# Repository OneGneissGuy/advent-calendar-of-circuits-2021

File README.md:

# advent-calendar-of-circuits-2021
Challenge to build a circuit board design and layout each day (on average) for 31 days in December. most of these circuits are based around operational and instrumentation amplifiers, but there are a few others that are more complex.

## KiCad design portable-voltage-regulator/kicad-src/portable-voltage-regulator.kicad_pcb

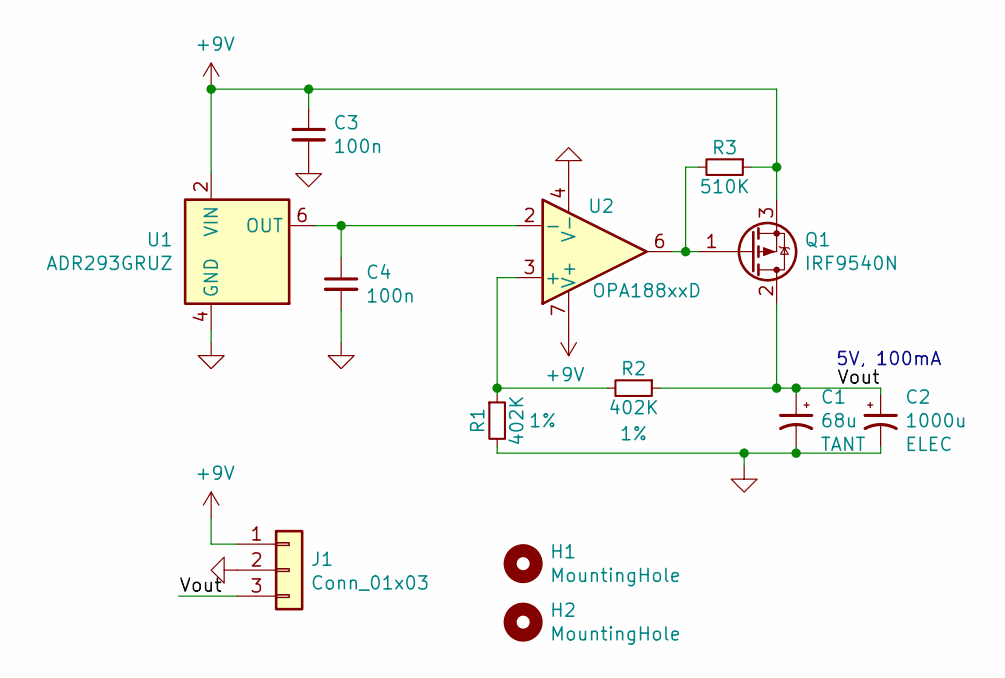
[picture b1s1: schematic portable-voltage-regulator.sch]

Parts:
C1: 68u; CP_EIA-3528-12_Kemet-T_Pad1.50x2.35mm_HandSolder
C2: 1000u; CP_Elec_6.3x5.4_Nichicon
C3, C4: 100n; C_0603_1608Metric
H1, H2: MountingHole; MountingHole_2.7mm_M2.5
J1: Conn_01x03; PinSocket_1x03_P2.54mm_Vertical
Q1: IRF9540N; TO-220-3_Vertical
R1, R2: 402K; R_0603_1608Metric
R3: 510K; R_0603_1608Metric
U1: ADR293GRUZ; TSSOP-8_4.4x3mm_P0.65mm
U2: OPA188xxD; SOIC-8_3.9x4.9mm_P1.27mm

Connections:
+9V: C3.1, J1.1, Q1.3 (S), R3.1, U1.2 (VIN), U2.7 (V+)
/Vout: C1.1, C2.1, J1.3, Q1.2 (D), R2.1
GND: C1.2, C2.2, C3.2, C4.2, J1.2, R1.2, U1.4 (GND), U2.4 (V-)
unnamed: C4.1, U1.6 (OUT), U2.2 (-)
unnamed: Q1.1 (G), R3.2, U2.6
unnamed: R1.1, R2.2, U2.3 (+)

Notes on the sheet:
5V, 100mA

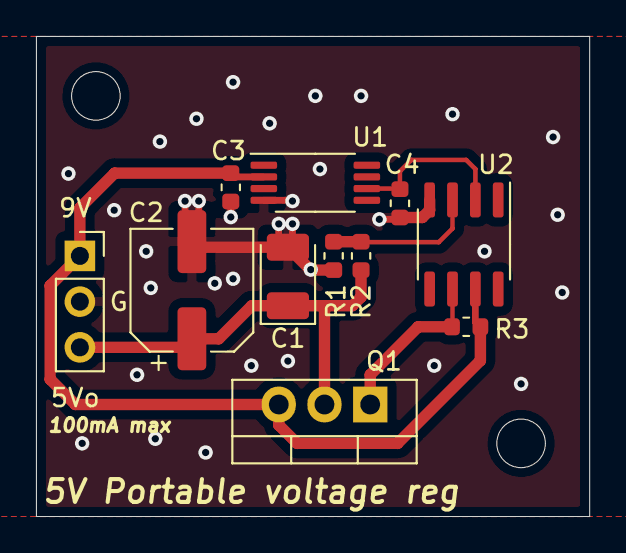
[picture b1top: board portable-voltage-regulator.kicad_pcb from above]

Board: 2 copper layers, 30.7 x 26.7 mm, 13 parts (0 on the bottom side), 6 nets.

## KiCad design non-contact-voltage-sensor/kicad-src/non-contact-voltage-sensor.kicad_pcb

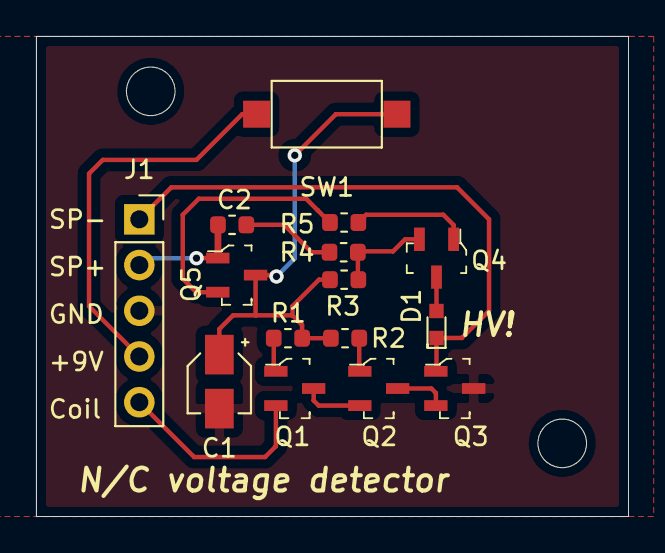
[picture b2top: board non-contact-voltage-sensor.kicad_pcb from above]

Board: 2 copper layers, 32.9 x 26.7 mm, 17 parts (0 on the bottom side), 15 nets.

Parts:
C1: 10uF; CP_Elec_3x5.3
C2: 47nF; C_0603_1608Metric
D1: LED_ALT; LED_0603
H1, H2: MountingHole; MountingHole_2.7mm_M2.5
J1: Conn_01x05; PinSocket_1x05_P2.54mm_Vertical
Q1, Q2, Q3, Q4: BC547BTA; SOT-23-3
Q5: BC557BTA; SOT-23-3
R1: 1M; R_0603_1608Metric
R2: 100K; R_0603_1608Metric
R3: 56K; R_0603_1608Metric
R4: 1K; R_0603_1608Metric
R5: 100R; R_0603_1608Metric
SW1: SW_SPST; SW_SPST_CK_RS282G05A3

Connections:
+9V: J1.4, SW1.2
/Coil: J1.5, Q1.2
/SP+: C2.2, J1.2, Q5.1
/SP-: D1.1, J1.1, Q3.1
GND: C1.2, J1.3, Q3.3
unnamed: C1.1, Q5.3, R1.1, R2.1, R3.1, SW1.1
unnamed: C2.1, R4.1
unnamed: D1.2, Q4.3
unnamed: Q1.1, R1.2
unnamed: Q1.3, Q2.2
unnamed: Q2.1, R2.2
unnamed: Q2.3, Q3.2
unnamed: Q4.1, R5.2
unnamed: Q4.2, R3.2, R4.2
unnamed: Q5.2, R5.1

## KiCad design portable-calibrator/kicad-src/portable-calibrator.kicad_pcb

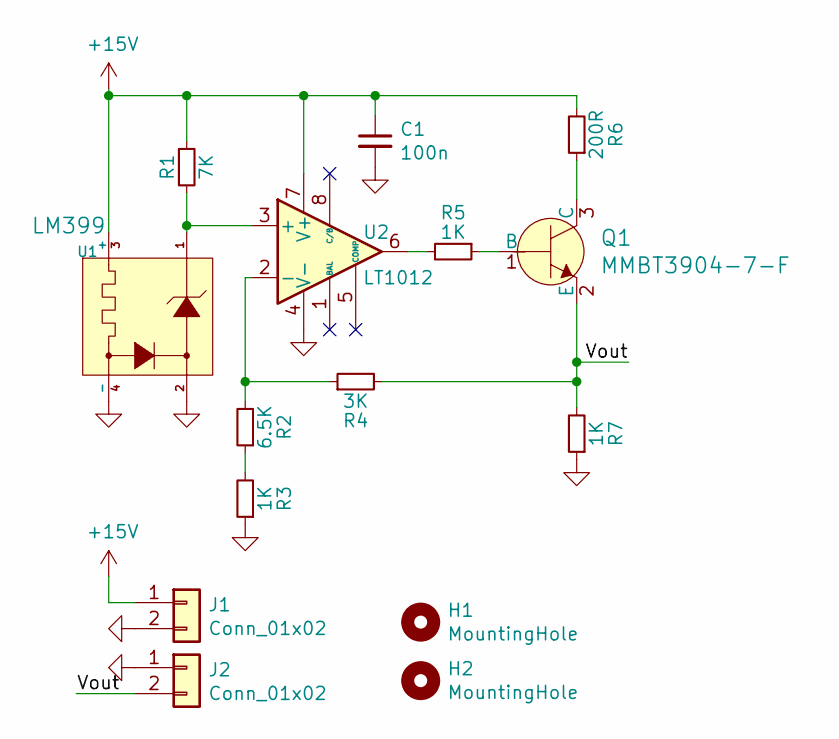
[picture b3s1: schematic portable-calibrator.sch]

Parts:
C1: 100n; C_0603_1608Metric
H1, H2: MountingHole; MountingHole_2.7mm_M2.5
J1, J2: Conn_01x02; PinSocket_1x02_P2.54mm_Vertical
Q1: MMBT3904-7-F; SOT-23-3; MPN MMBT3904-7-F; Digi-Key_PN MMBT3904-FDICT-ND
R1: 7K; R_0603_1608Metric
R2: 6.5K; R_0603_1608Metric
R3, R5, R7: 1K; R_0603_1608Metric
R4: 3K; R_0603_1608Metric
R6: 200R; R_0603_1608Metric
U1: LM399; TO-46-4
U2: LT1012; SOIC-8_3.9x4.9mm_P1.27mm

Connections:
+15V: C1.1, J1.1, R1.1, R6.2, U1.3 (+), U2.7 (V+)
/Vout: J2.2, Q1.2 (E), R4.2, R7.2
GND: C1.2, J1.2, J2.1, R3.1, R7.1, U1.2, U1.4 (-), U2.4 (V-)
unnamed: Q1.1 (B), R5.1
unnamed: Q1.3 (C), R6.1
unnamed: R1.2, U1.1, U2.3 (+)
unnamed: R2.1, R3.2
unnamed: R2.2, R4.1, U2.2 (-)
unnamed: R5.2, U2.6

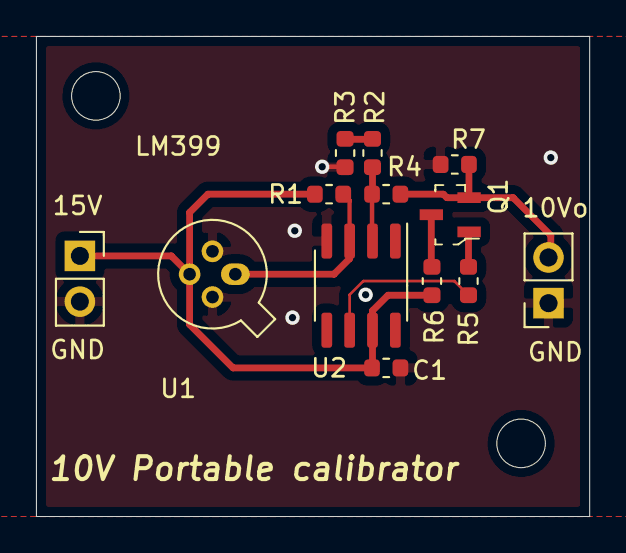
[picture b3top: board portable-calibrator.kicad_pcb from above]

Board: 2 copper layers, 30.7 x 26.7 mm, 15 parts (0 on the bottom side), 9 nets.

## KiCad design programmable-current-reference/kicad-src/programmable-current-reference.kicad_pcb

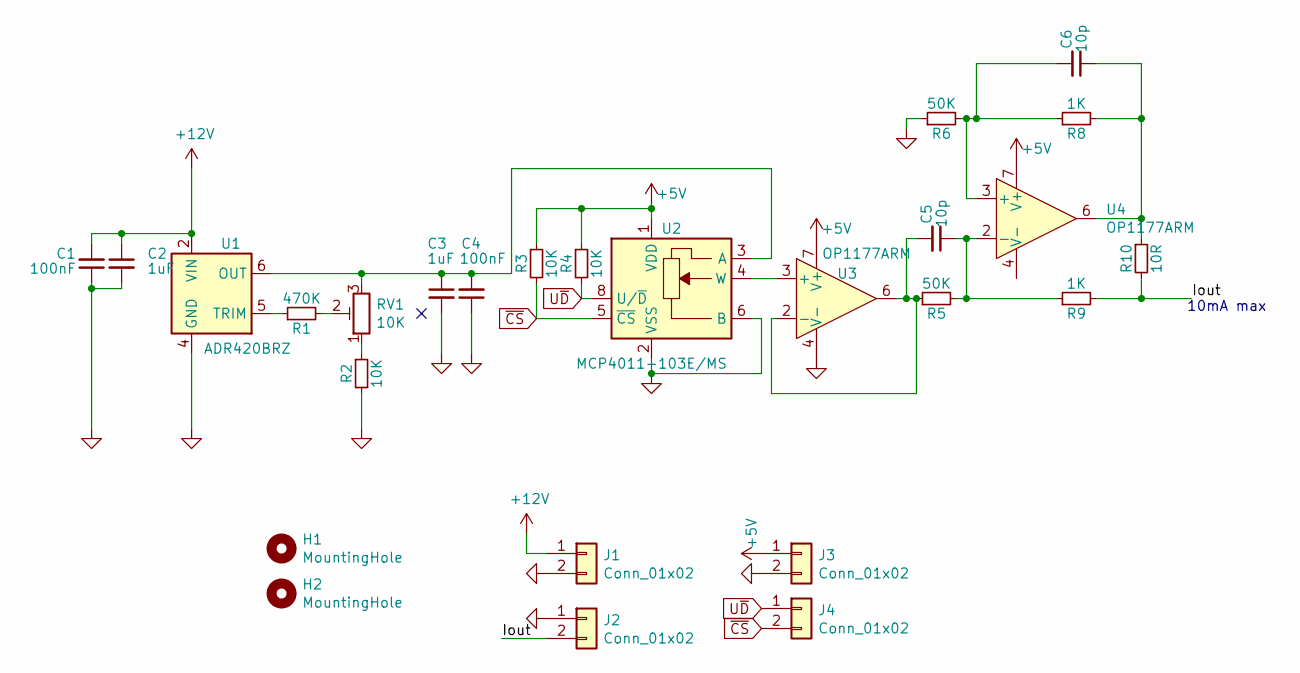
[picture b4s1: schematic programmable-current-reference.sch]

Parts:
C1, C4: 100nF; C_0603_1608Metric
C2, C3: 1uF; C_0603_1608Metric
C5, C6: 10p; C_0603_1608Metric
H1, H2: MountingHole; MountingHole_2.7mm_M2.5
J1, J2, J3, J4: Conn_01x02; PinHeader_1x02_P2.54mm_Vertical
R1: 470K; R_0603_1608Metric
R2, R3, R4: 10K; R_0603_1608Metric
R5, R6: 50K; R_0603_1608Metric
R8, R9: 1K; R_0603_1608Metric
R10: 10R; R_0603_1608Metric
RV1: 10K; Potentiometer_Bourns_3266W_Vertical
U1: ADR420BRZ; MSOP-8_3x3mm_P0.65mm
U2: MCP4011-103E/MS; MSOP-8_3x3mm_P0.65mm
U3, U4: OP1177ARM; MSOP-8_3x3mm_P0.65mm

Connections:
+5V: J3.1, R3.1, R4.1, U2.1 (VDD), U3.7 (V+), U4.7 (V+)
+12V: C1.2, C2.1, J1.1, U1.2 (VIN)
/Iout: J2.2, R9.2, R10.2
GND: C1.1, C2.2, C3.2, C4.1, J1.2, J2.1, J3.2, R2.2, R6.1, U1.4 (GND), U2.2 (VSS), U2.6 (B), U3.4 (V-)
unnamed: C3.1, C4.2, RV1.3, U1.6 (OUT), U2.3 (A)
unnamed: C5.1, R5.2, R9.1, U4.2 (-)
unnamed: C5.2, R5.1, U3.2 (-), U3.6
unnamed: C6.1, R8.2, R10.1, U4.6
unnamed: C6.2, R6.2, R8.1, U4.3 (+)
unnamed: R1.1, U1.5 (TRIM)
unnamed: R1.2, RV1.2
unnamed: R2.1, RV1.1
unnamed: U2.4 (W), U3.3 (+)
U~D: J4.1, R4.2, U2.8 (U/~D)
~CS: J4.2, R3.2, U2.5 (~CS)

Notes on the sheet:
10mA max

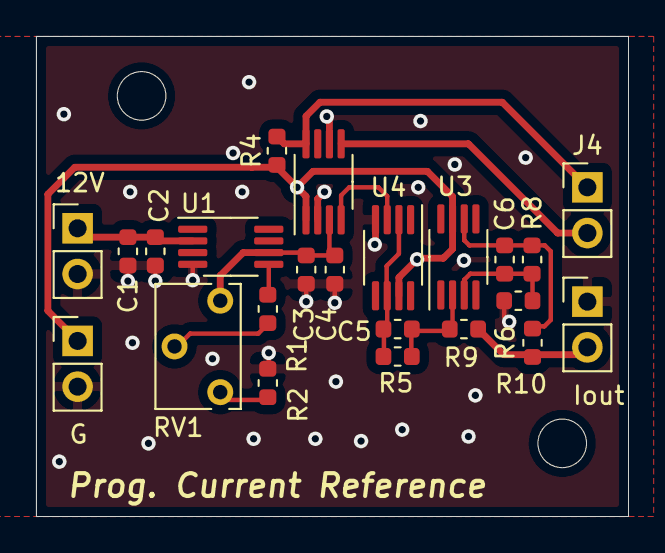
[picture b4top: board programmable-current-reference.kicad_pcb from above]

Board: 2 copper layers, 32.9 x 26.7 mm, 25 parts (0 on the bottom side), 15 nets.

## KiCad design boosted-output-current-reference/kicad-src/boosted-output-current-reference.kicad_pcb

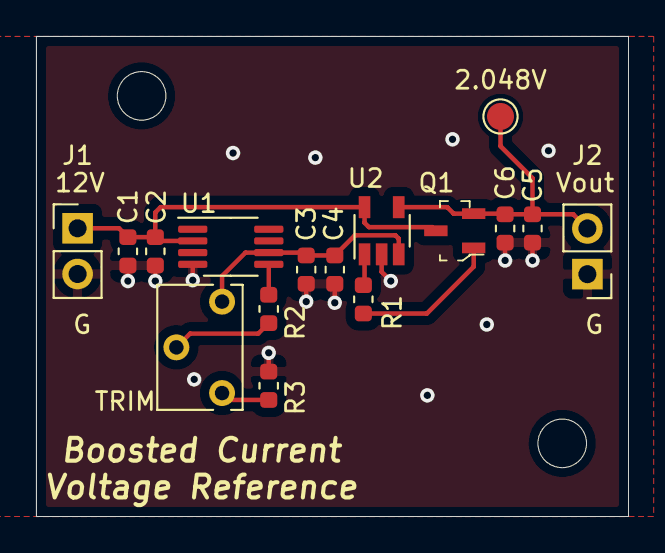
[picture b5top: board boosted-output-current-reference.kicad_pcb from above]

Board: 2 copper layers, 32.9 x 26.7 mm, 18 parts (0 on the bottom side), 9 nets.

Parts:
2.048V: TestPoint; TestPoint_Pad_D1.5mm
C1, C4, C5: 1uF; C_0603_1608Metric
C2, C3, C6: 100nF; C_0603_1608Metric
H1, H2: MountingHole; MountingHole_2.7mm_M2.5
J1, J2: Conn_01x02; PinHeader_1x02_P2.54mm_Vertical
Q1: 2N7002; SOT-23-3
R1: 100R; R_0603_1608Metric
R2: 470K; R_0603_1608Metric
R3: 10K; R_0603_1608Metric
TRIM: 10K; Potentiometer_Bourns_3266W_Vertical
U1: ADR420BRZ; MSOP-8_3x3mm_P0.65mm
U2: AD8603; TSOT-23-5

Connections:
+12V: C1.1, C2.2, J1.1, Q1.3, U1.2, U2.5
/Vout: 2.048V.1, C5.1, C6.1, J2.2, Q1.2, U2.4
GND: C1.2, C2.1, C3.1, C4.2, C5.2, C6.2, J1.2, J2.1, R3.2, U1.4, U2.2
unnamed: C3.2, C4.1, TRIM.3, U1.6, U2.3
unnamed: Q1.1, R1.2
unnamed: R1.1, U2.1
unnamed: R2.1, U1.5
unnamed: R2.2, TRIM.2
unnamed: R3.1, TRIM.1

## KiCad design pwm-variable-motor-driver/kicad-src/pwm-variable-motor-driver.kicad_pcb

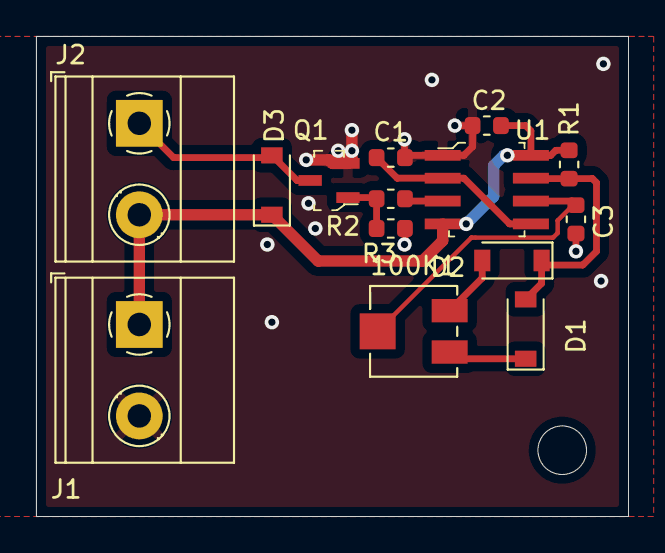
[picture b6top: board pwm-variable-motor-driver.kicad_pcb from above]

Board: 2 copper layers, 32.9 x 26.7 mm, 15 parts (0 on the bottom side), 10 nets.

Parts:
100K1: R_POT_TRIM; Potentiometer_Bourns_3214J_Horizontal
C1: 10n; C_0603_1608Metric
C2, C3: 100n; C_0603_1608Metric
D1, D2, D3: D_Small; D_SOD-123
H1: MountingHole; MountingHole_2.7mm_M2.5
J1, J2: Conn_01x02; TerminalBlock_Phoenix_MKDS-1,5-2-5.08_1x02_P5.08mm_Horizont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
Q1: AO3401A; SOT-23-3
R1, R2: 1K; R_0603_1608Metric
R3: 10K; R_0603_1608Metric
U1: NE555DR; SOIC-8_W3.9mm

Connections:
+12V: C2.1, D3.1, J1.1, J2.2, R1.1, U1.4, U1.8
/M-: D3.2, J2.1, Q1.3
GND: C1.2, C2.2, C3.2, J1.2, Q1.2, R3.2, U1.1
unnamed: 100K1.1, D2.2
unnamed: 100K1.2, C3.1, U1.6
unnamed: 100K1.3, D1.1
unnamed: C1.1, U1.2, U1.5
unnamed: D1.2, D2.1, R1.2, U1.7
unnamed: Q1.1, R2.2, R3.1
unnamed: R2.1, U1.3

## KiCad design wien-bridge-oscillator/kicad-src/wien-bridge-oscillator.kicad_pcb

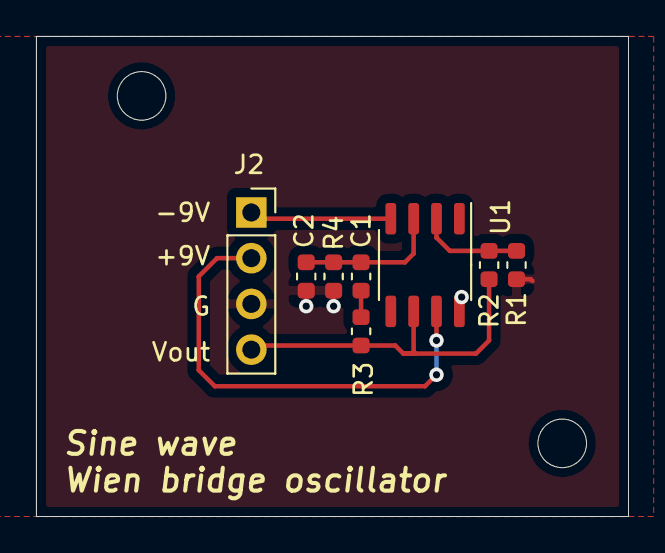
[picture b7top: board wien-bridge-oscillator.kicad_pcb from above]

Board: 2 copper layers, 32.9 x 26.7 mm, 10 parts (0 on the bottom side), 7 nets.

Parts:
C1, C2: 10nF; C_0603_1608Metric
H1, H2: MountingHole; MountingHole_2.7mm_M2.5
J2: Conn_01x04; PinSocket_1x04_P2.54mm_Vertical
R1, R2, R3, R4: 10K; R_0603_1608Metric
U1: TL081; SO-8_3.9x4.9mm_P1.27mm

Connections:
+9V: J2.2, U1.7
-9V: J2.1, U1.4
/Vout: J2.4, R2.2, R3.1, U1.6
GND: C2.1, J2.3, R1.1, R4.2
unnamed: C1.1, C2.2, R4.1, U1.3
unnamed: C1.2, R3.2
unnamed: R1.2, R2.1, U1.2

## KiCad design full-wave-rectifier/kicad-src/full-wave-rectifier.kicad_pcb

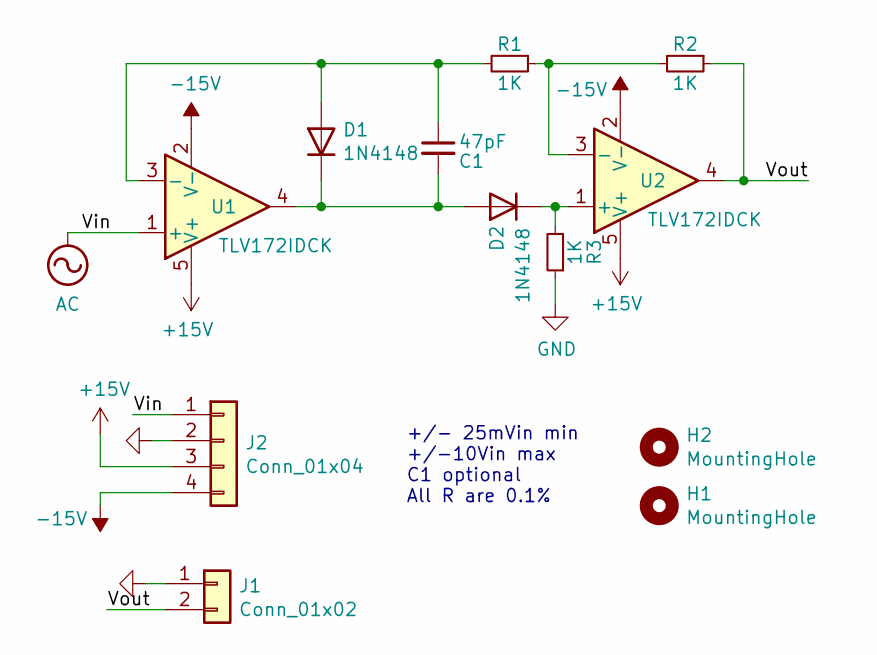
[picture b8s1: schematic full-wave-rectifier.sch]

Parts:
C1: 47pF; C_0603_1608Metric
D1, D2: 1N4148; D_SOD-323_HandSoldering
H1, H2: MountingHole; MountingHole_2.7mm_M2.5
J1: Conn_01x02; PinSocket_1x02_P2.54mm_Vertical
J2: Conn_01x04; PinSocket_1x04_P2.54mm_Vertical
R1, R2, R3: 1K; R_0603_1608Metric
U1, U2: TLV172IDCK; SOT-353_SC-70-5

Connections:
+15V: J2.3, U1.5 (V+), U2.5 (V+)
-15V: J2.4, U1.2 (V-), U2.2 (V-)
/Vout: J1.2, R2.1, U2.4
AC: J2.1, U1.1 (+)
GND: J1.1, J2.2, R3.1
unnamed: C1.1, D1.2 (A), R1.2, U1.3 (-)
unnamed: C1.2, D1.1 (K), D2.2 (A), U1.4
unnamed: D2.1 (K), R3.2, U2.1 (+)
unnamed: R1.1, R2.2, U2.3 (-)

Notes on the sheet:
+/- 25mVin min +/-10Vin max C1 optional All R are 0.1%

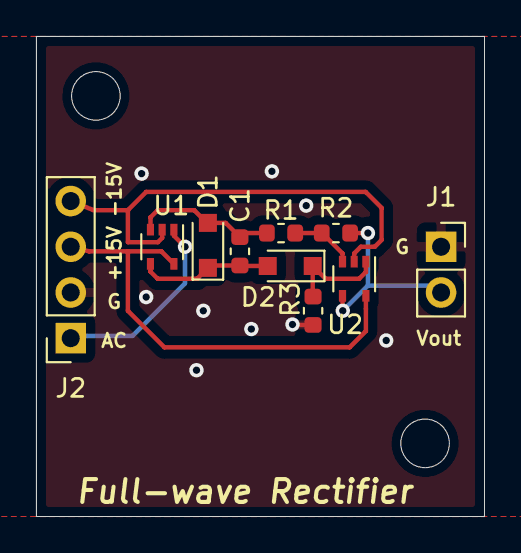
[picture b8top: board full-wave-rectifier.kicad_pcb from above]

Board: 2 copper layers, 24.9 x 26.7 mm, 12 parts (0 on the bottom side), 9 nets.

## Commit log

2021-12-02 adds day1 current sense board
2021-12-02 moves max4209 symbol FB terminals
2021-12-02 stabilizes output with cap on FB pin
2021-12-03 adds so8 3d model
2021-12-03 create day 2 peak detector
2021-12-04 creates TC amp
2021-12-04 adds guard trace and prod files
2021-12-04 adds render
2021-12-05 day 4 opamp low side current sense
2021-12-05 fix silkscreen error
2021-12-08 adds photodiode amp
2021-12-08 updates tc amp gerbers
2021-12-08 creates pd amp prod files
2021-12-08 update component values and ids
2021-12-08 adds full wave rectifier
2021-12-08 adds wien bridge osc
2021-12-09 creates boosted current output vref
2021-12-14 layout nc voltage sensor
2021-12-14 update render and prod files for diode
2021-12-14 update silkscreen for prod files
2021-12-14 adds portable calibrator
2021-12-20 creates pwm variable motor driver
2021-12-21 minor change to pwm vr 3d model
2021-12-21 add trim to v reference
2021-12-22 current ref
2021-12-22 reroute portable calibrator
2021-12-22 adds portable vreg
2021-12-22 updates prod nc volt sensor
2021-12-22 upgrade opamp
